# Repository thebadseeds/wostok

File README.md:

## Wostok
### Open Hardware Analog Synthesizer

PCB created with KiCad

This semi-maintained repository is aimed towards people that want to hack their own analog synthesizer using the XR2206 voltage controlled oscillator. 

It uses simple analog filter designs that are controlled using light-dependend resistors. The design is working but is kind off glitching out when using switching/unclean control voltages (ie when using an Arduino).

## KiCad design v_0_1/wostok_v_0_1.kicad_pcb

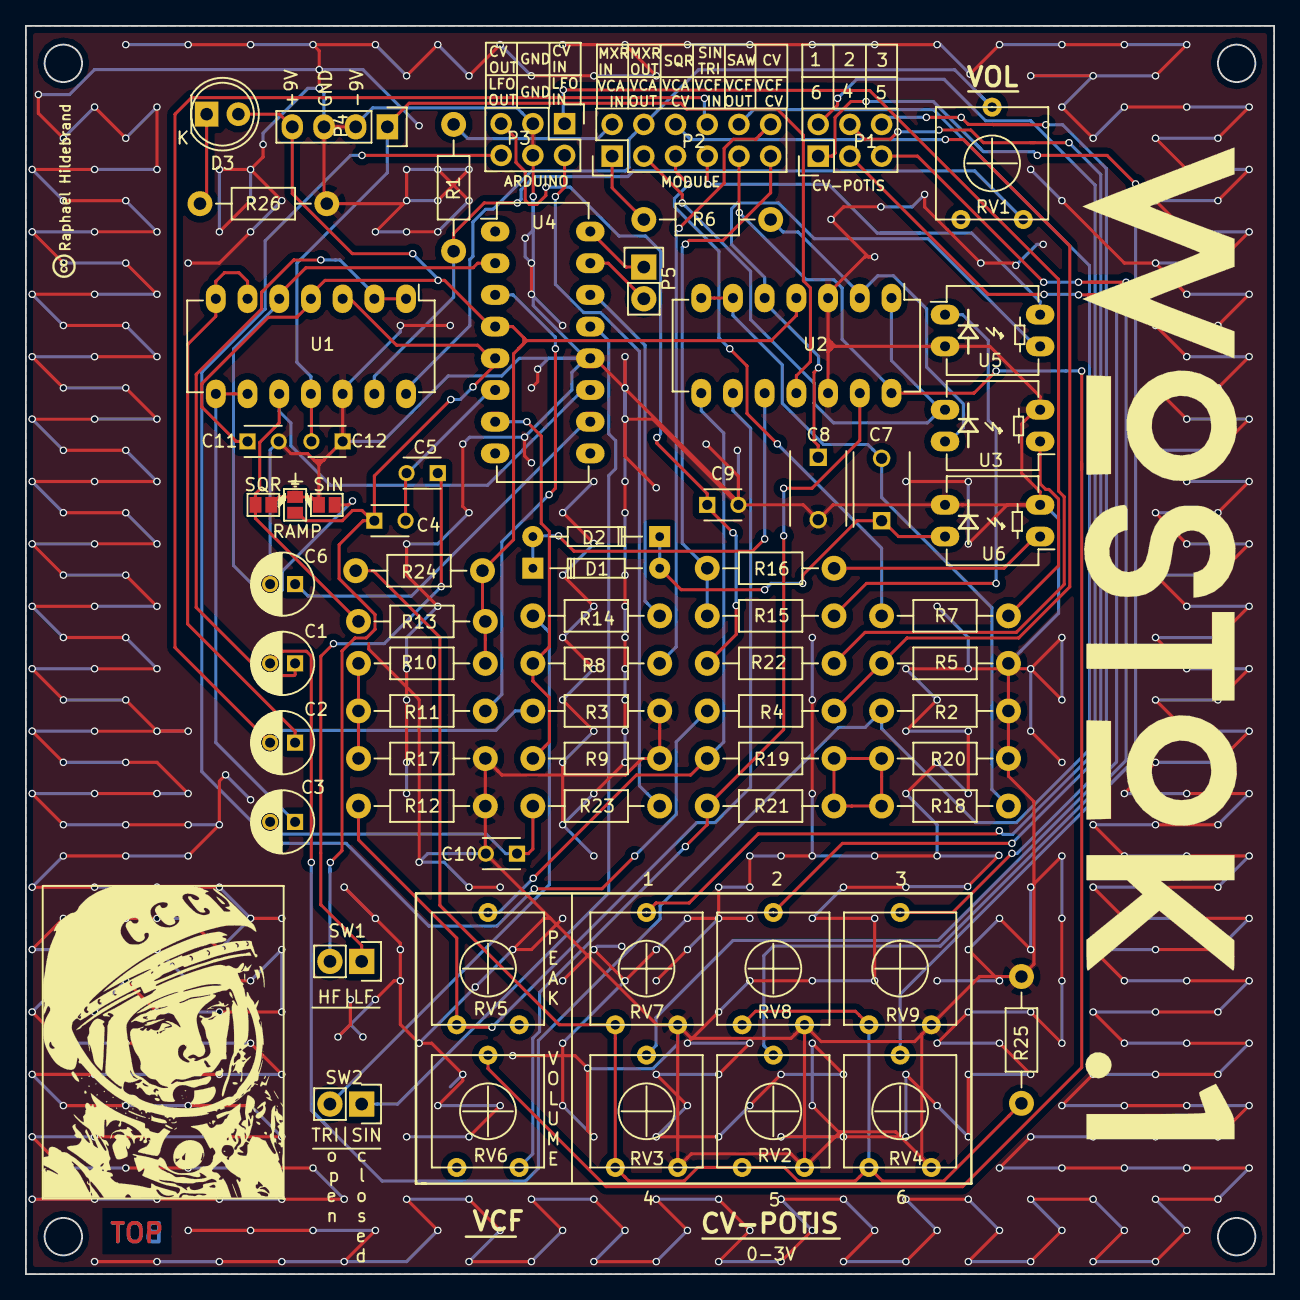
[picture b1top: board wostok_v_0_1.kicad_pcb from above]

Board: 2 copper layers, 100.0 x 100.0 mm, 66 parts (0 on the bottom side), 58 nets.

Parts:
C1, C2, C3, C6: 1u; C_Radial_D5_L11_P2
C4, C9, C10, C11, C12: 100n; C_Disc_D3_P2.5
C5: 220n; C_Disc_D3_P2.5
C7, C8: 10n; C_Disc_D6_P5
D1, D2: 1N4148; Diode_DO-35_SOD27_Horizontal_RM10
D3: Led_Small; LED-5MM
GS1, GS2, GS3: GS2
P1, P3: CONN_02X03; Pin_Header_Straight_2x03
P2: CONN_02X06; Pin_Header_Straight_2x06
P4: CONN_01X04; Pin_Header_Straight_1x04
P5: CONN_01X02; Pin_Header_Straight_1x02
R1, R2, R3, R9, R11, R13, R17, R22, R23: 10k; Resistor_Horizontal_RM10mm
R4: 8k; Resistor_Horizontal_RM10mm
R5, R18, R19: 2k; Resistor_Horizontal_RM10mm
R6: 22k; Resistor_Horizontal_RM10mm
R7, R15, R16: 250; Resistor_Horizontal_RM10mm
R8: 533; Resistor_Horizontal_RM10mm
R10, R12: 4.9k; Resistor_Horizontal_RM10mm
R14: 200; Resistor_Horizontal_RM10mm
R20, R26: 1k; Resistor_Horizontal_RM10mm
R21, R25: 20k; Resistor_Horizontal_RM10mm
R24: 60k; Resistor_Horizontal_RM10mm
RV1: 20k; ACP14-L
RV2, RV3, RV4, RV5, RV6, RV7, RV8, RV9: 100k; ACP14-L
SW1, SW2: SPST; Pin_Header_Straight_1x02
U1, U2: LM2902N; DIP-14_W7.62mm_LongPads
U3, U5, U6: NSL-32; DIP-4_W7.62mm_LongPads
U4: XR2206; DIP-16_W7.62mm_LongPads

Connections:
+9VA: C11.1, D3.2, P4.4, R10.2, R13.2, R24.1, U1.4, U2.4, U4.4
-9VA: C12.2, P4.1, U1.11, U2.11
/+3V: R24.2, R25.1, RV2.1, RV3.1, RV4.1, RV7.1, RV8.1, RV9.1
/SQUARE: GS3.2, R13.1, U1.10, U4.11
/TC1: C4.1, GS1.1, SW1.2, U1.3, U4.5
/TRI/SINE: GS2.2, U1.5, U4.2
/VERSORGUNG_UND_CV/CVIN: P3.1, R22.2
/VERSORGUNG_UND_CV/CVOUT: C9.1, P3.5, R22.1
/VERSORGUNG_UND_CV/LFOIN: P3.2, R23.2
/VERSORGUNG_UND_CV/LFOOUT: C10.1, P3.6, R23.1
CV: P2.12, R8.2
GND: C6.2, C7.2, C9.2, C10.2, C11.2, C12.1, GS1.2, GS2.1, GS3.1, P3.3, P3.4, P4.2, P4.3, R2.1, R3.2, R5.2, R9.2, R12.1, R17.2, R20.2, R25.2, R26.2, RV2.3, RV3.3, RV4.3, RV7.3, RV8.3, RV9.3, U1.12, U2.3, U2.12, U3.2, U4.12, U5.2, U6.2, U6.3
MXR_IN: P2.2, R1.2
MXR_OUT: P2.4, RV1.2, U1.14
unnamed: C1.1, U1.1, U1.2
unnamed: C2.1, U1.6, U1.7
unnamed: C3.1, U1.8, U1.9
unnamed: C3.2, R4.1
unnamed: C4.2, C5.2, U4.6
unnamed: C5.1, SW1.1
unnamed: C6.1, U4.10
unnamed: C7.1, U2.5, U5.3
unnamed: C8.1, D1.2, D2.1, U6.4
unnamed: C8.2, R18.2, U2.6, U2.7
unnamed: D1.1, D2.2, U2.10
unnamed: D3.1, R26.1
unnamed: P1.1, RV4.2
unnamed: P1.2, RV7.2
unnamed: P1.3, RV3.2
unnamed: P1.4, RV8.2
unnamed: P1.5, RV2.2
unnamed: P1.6, RV9.2
unnamed: P5.1, U4.16
unnamed: P5.2, U4.15
unnamed: R1.1, RV1.3, U1.13
unnamed: R6.1, U2.2, U3.4
unnamed: R7.2, U3.1
unnamed: R8.1, R9.1, U4.7
unnamed: R10.1, R11.2, R12.2
unnamed: R11.1, U4.3
unnamed: R14.1, SW2.2
unnamed: R14.2, U4.14
unnamed: R15.1, U5.1
unnamed: R16.1, U6.1
unnamed: R17.1, RV5.1, U2.9
unnamed: R18.1, R19.2, R20.1, R21.2
unnamed: R19.1, RV5.2, U2.8
unnamed: R21.1, RV6.3, U2.13
unnamed: SW2.1, U4.13
RAMPOID: C1.2, P2.10, R2.2
SQR: P2.6, R4.2, R5.1
TRI/SIN: C2.2, P2.8, R3.1
VCA_CV: P2.5, R7.1
VCA_IN: P2.1, R6.2
VCA_OUT: P2.3, U2.1, U3.3
VCF_CV: P2.11, R15.2, R16.2
VCF_IN: P2.7, U5.4
VCF_OUT: P2.9, RV6.2, U2.14

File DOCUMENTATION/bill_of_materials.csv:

Id,Designator,Quantity,Designation,Package,Supplier and ref
1,RV1,1,20k,ACP14-L,
2,"RV5,RV2,RV3,RV4,RV6,RV7,RV8,RV9",8,100k,ACP14-L,
3,"U6,U3,U5",3,NSL-32,DIP-4_W7.62mm_LongPads,
4,"C1,C2,C3,C6",4,1u,C_Radial_D5_L11_P2,
5,"C4,C9,C10,C11,C12",5,100n,C_Disc_D3_P2.5,
6,C5,1,220n,C_Disc_D3_P2.5,
7,"C7,C8",2,10n,C_Disc_D6_P5,
8,"D1,D2",2,1N4148,Diode_DO-35_SOD27_Horizontal_RM10,
9,"GS1,GS2,GS3",3,GS2,GS2,
10,P2,1,CONN_02X06,Pin_Header_Straight_2x06,
11,P5,1,CONN_01X02,Pin_Header_Straight_1x02,
12,"U1,U2",2,LM2902N,DIP-14_W7.62mm_LongPads,
13,U4,1,XR2206,DIP-16_W7.62mm_LongPads,
14,"R1,R2,R3,R9,R11,R13,R17,R22,R23",9,10k,Resistor_Horizontal_RM10mm,
15,R4,1,8k,Resistor_Horizontal_RM10mm,
16,"R5,R18,R19",3,2k,Resistor_Horizontal_RM10mm,
17,R6,1,22k,Resistor_Horizontal_RM10mm,
18,"R7,R15,R16",3,250,Resistor_Horizontal_RM10mm,
19,R8,1,533,Resistor_Horizontal_RM10mm,
20,"R10,R12",2,4.9k,Resistor_Horizontal_RM10mm,
21,R14,1,200,Resistor_Horizontal_RM10mm,
22,"R20,R26",2,1k,Resistor_Horizontal_RM10mm,
23,"R21,R25",2,20k,Resistor_Horizontal_RM10mm,
24,"P1,P3",2,CONN_02X03,Pin_Header_Straight_2x03,
25,P4,1,CONN_01X04,Pin_Header_Straight_1x04,
26,R24,1,60k,Resistor_Horizontal_RM10mm,
27,D3,1,Led_Small,LED-5MM,
28,"SW1,SW2",2,SPST,Pin_Header_Straight_1x02,

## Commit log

2016-03-26 finished v0.1
    finished PCB including external LFO/CV input, VCF, VCA, VCO, mixer and some potentiometers. fully patchable using jumper wires.
2016-03-26 deleted redundant file
2016-03-26 documentation
    under progress
2016-03-26 just renamed the folders
2016-03-31 changed folder structure + added folder for arduino software
2016-04-01 new readme for software part
2016-04-01 First draft for midi interface.
2016-04-05 added BOM
2016-04-05 added pcb creater info
2016-04-05 added gitignore
2016-04-05 added pinModes added output ControlVOltage
2016-04-06 fixed wrong silkscreen of vactrols
2016-04-09 added untested ADSR support
2016-04-09 test software
2016-04-09 minor refinements
2020-03-05 Added information and images
2020-03-05 Markup magic
2020-03-05 Markdown magic
